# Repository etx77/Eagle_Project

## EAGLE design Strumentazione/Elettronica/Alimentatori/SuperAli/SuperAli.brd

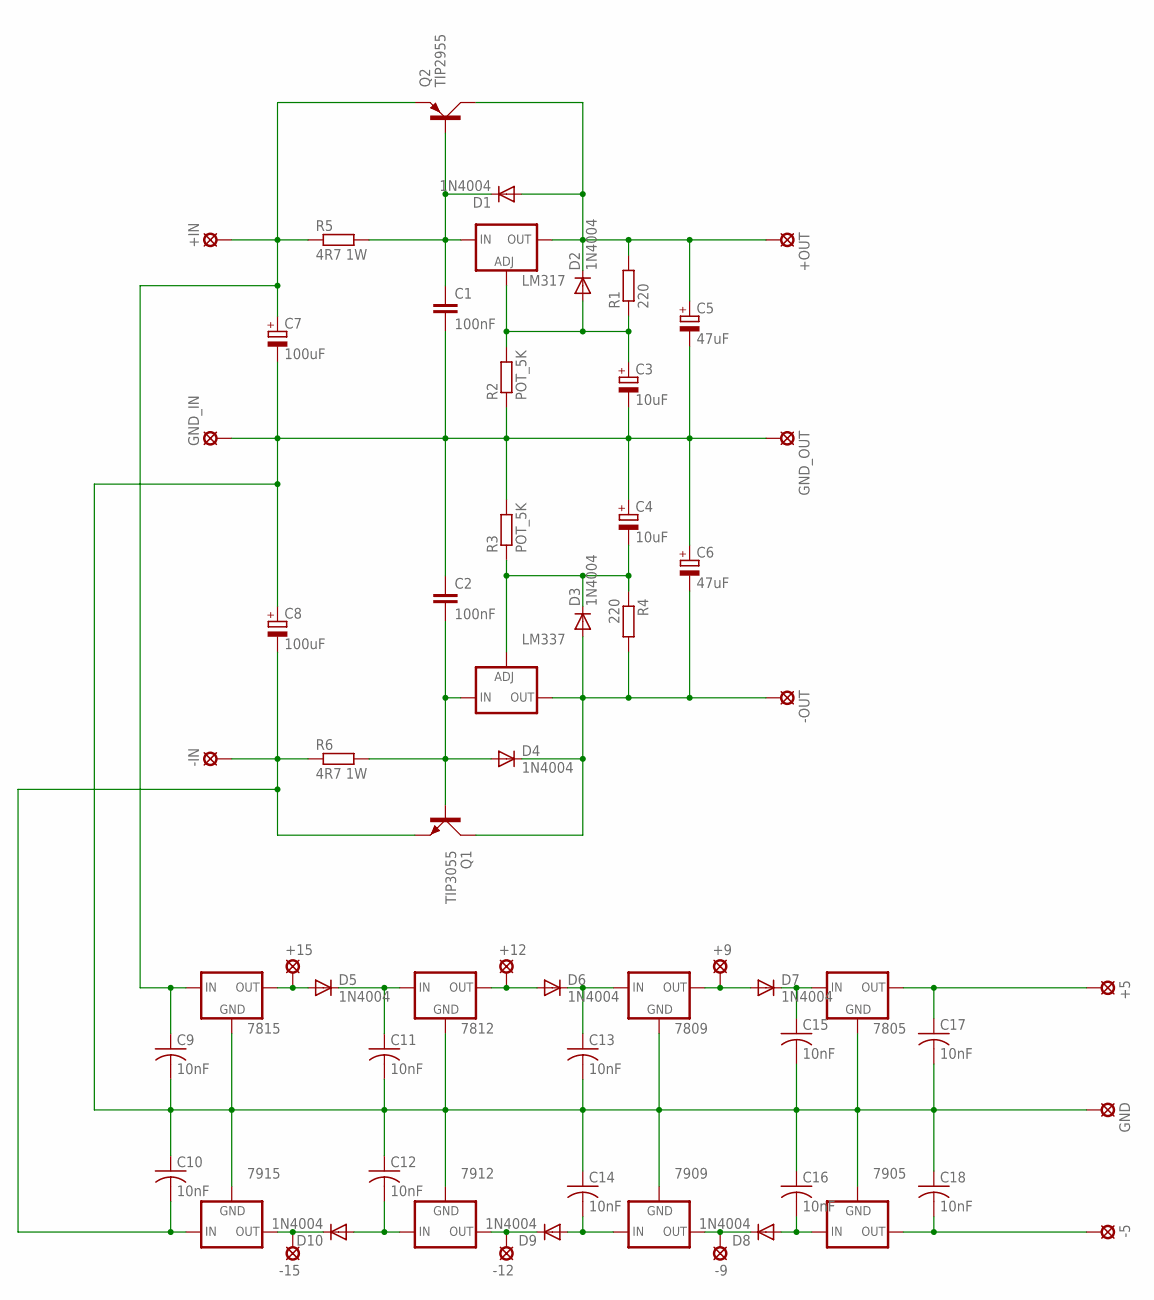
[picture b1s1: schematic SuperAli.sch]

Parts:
7805, 7809, 7812, 7815: 78XXS
7905, 7909, 7912, 7915: 79XXS
+5, +9, +12, +15: LSP10
+IN: LSP13
+OUT: LSP13
-5, -9, -12, -15: LSP10
-IN: LSP13
-OUT: LSP13
C1, C2: 100nF; C025-040X050
C3, C4: 10uF; E2-5
C5, C6: 47uF; E3,5-10
C7, C8: 100uF; E7,5-16
C9, C10, C11, C12, C13, C14, C15, C16, C17, C18: 10nF; C025-025X050
D1, D2, D3, D4, D5, D6, D7, D8, D9, D10: 1N4004; DO41-10
GND: LSP10
GND_IN: LSP13
GND_OUT: LSP13
LM317: LM317TS; 317TS
LM337: LM337TS; 337TS
Q1: TIP3055; TOP3AV
Q2: TIP2955; TOP3AV
R1, R4: 220; 0207/7
R2, R3: POT_5K; 0207/7
R5, R6: 4R7 1W; 0617/17

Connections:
7809: 7809.OUT, +9.MP, D7.A
unnamed: C3.+, D2.A, LM317.1 (ADJ), R1.1, R2.2
unnamed: C2.2, D4.A, LM337.2 (IN), Q1.B, R6.2
unnamed: C4.-, D3.C, LM337.1 (ADJ), R3.1, R4.1
unnamed: C1.1, D1.C, LM317.3 (IN), Q2.B, R5.2
unnamed: -OUT.MP, C6.-, D3.A, D4.C, LM337.3 (OUT), Q1.C, R4.2
unnamed: 7815.IN, +IN.MP, C7.+, C9.1, Q2.E, R5.1
unnamed: 7805.GND, 7809.GND, 7812.GND, 7815.GND, 7905.GND, 7909.GND, 7912.GND, 7915.GND, C1.2, C2.1, C3.-, C4.+, C5.-, C6.+, C7.-, C8.+, C9.2, C10.1, C11.2, C12.1, C13.2, C14.1, C15.2, C16.1, C17.2, C18.1, GND.MP, GND_IN.MP, GND_OUT.MP, R2.1, R3.2
unnamed: 7915.IN, -IN.MP, C8.-, C10.2, Q1.E, R6.1
unnamed: +OUT.MP, C5.+, D1.A, D2.C, LM317.2 (OUT), Q2.C, R1.2
unnamed: 7805.OUT, +5.MP, C17.1
unnamed: 7905.OUT, -5.MP, C18.2
unnamed: 7805.IN, C15.1, D7.C
unnamed: 7905.IN, C16.2, D8.A
unnamed: 7909.OUT, -9.MP, D8.C
unnamed: 7809.IN, C13.1, D6.C
unnamed: 7909.IN, C14.2, D9.A
unnamed: 7912.OUT, -12.MP, D9.C
unnamed: 7812.OUT, +12.MP, D6.A
unnamed: 7812.IN, C11.1, D5.C
unnamed: 7815.OUT, +15.MP, D5.A
unnamed: 7915.OUT, -15.MP, D10.C
unnamed: 7912.IN, C12.2, D10.A

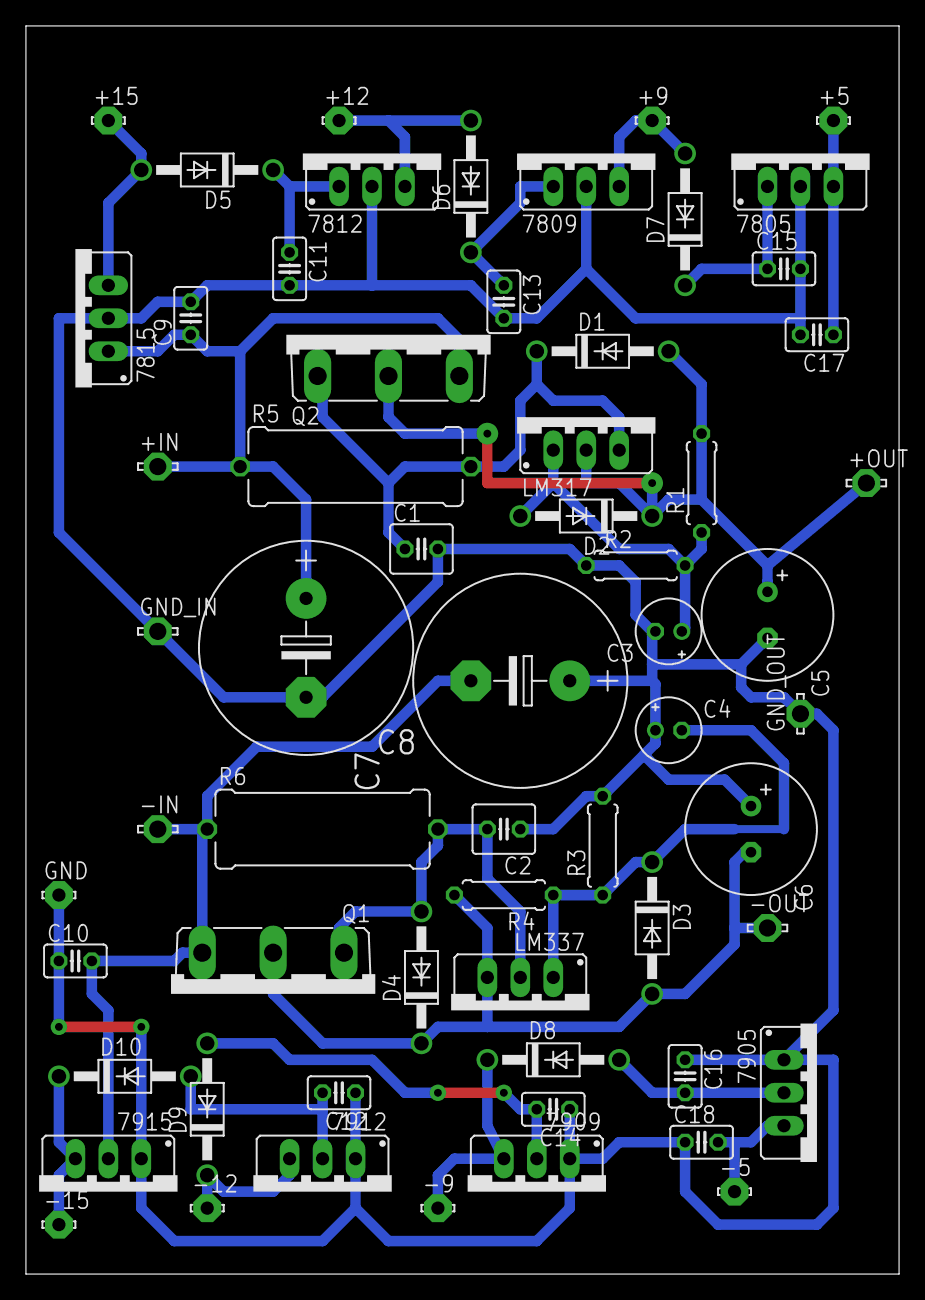
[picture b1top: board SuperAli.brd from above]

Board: 2 copper layers, 67.3 x 96.2 mm, 61 parts (0 on the bottom side), 23 nets.

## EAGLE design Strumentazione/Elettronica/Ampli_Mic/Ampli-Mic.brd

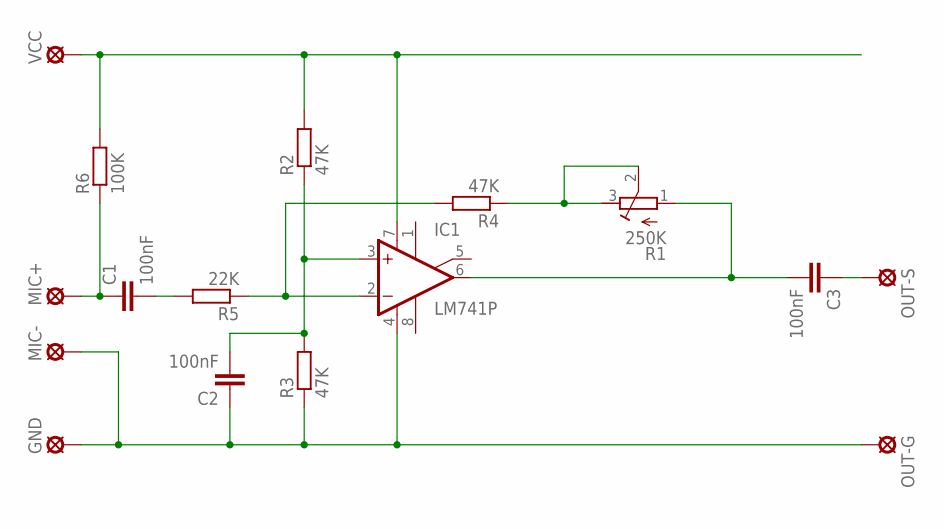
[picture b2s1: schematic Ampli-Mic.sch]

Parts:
C1, C2, C3: 100nF; C050-024X044
GND: LSP10
IC1: LM741P; DIL08
MIC+: LSP10
MIC-: LSP10
OUT-G: LSP10
OUT-S: LSP10
R1: 250K; RTRIM3339P
R2, R3, R4: 47K; 0207/10
R5: 22K; 0207/10
R6: 100K; 0207/10
VCC: LSP10

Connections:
unnamed: C2.1, GND.MP, IC1.4 (V-), MIC-.MP, OUT-G.MP, R3.1
unnamed: IC1.7 (V+), R2.2, R6.2, VCC.MP
unnamed: C2.2, IC1.3 (+IN), R2.1, R3.2
unnamed: IC1.2 (-IN), R4.2, R5.1
unnamed: R1.2 (S), R1.3 (E), R4.1
unnamed: C3.1, OUT-S.MP
unnamed: C3.2, IC1.6 (OUT), R1.1 (A)
unnamed: C1.2, R5.2
unnamed: C1.1, MIC+.MP, R6.1

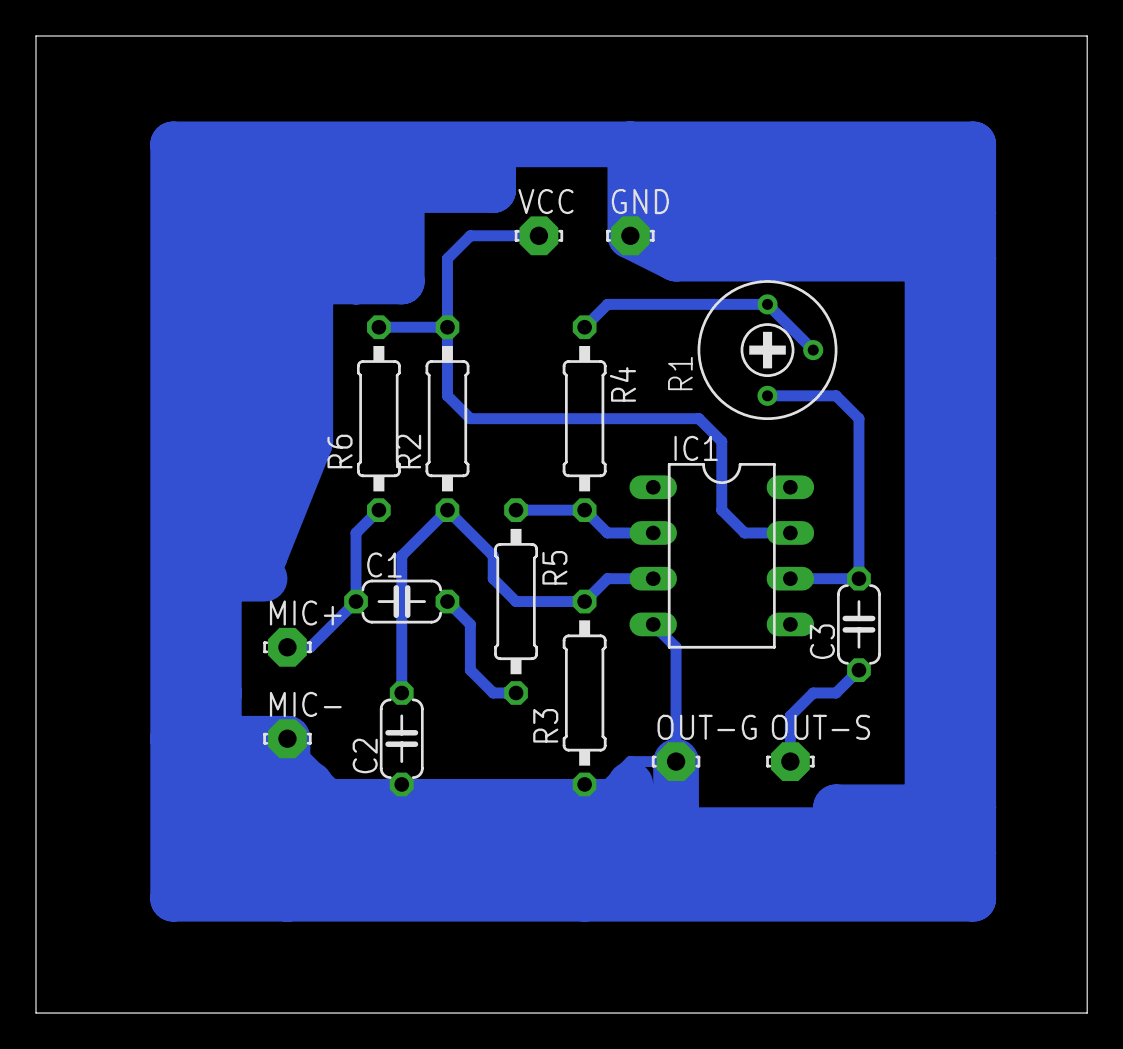
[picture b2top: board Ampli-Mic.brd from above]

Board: 2 copper layers, 58.4 x 54.3 mm, 16 parts (0 on the bottom side), 9 nets.

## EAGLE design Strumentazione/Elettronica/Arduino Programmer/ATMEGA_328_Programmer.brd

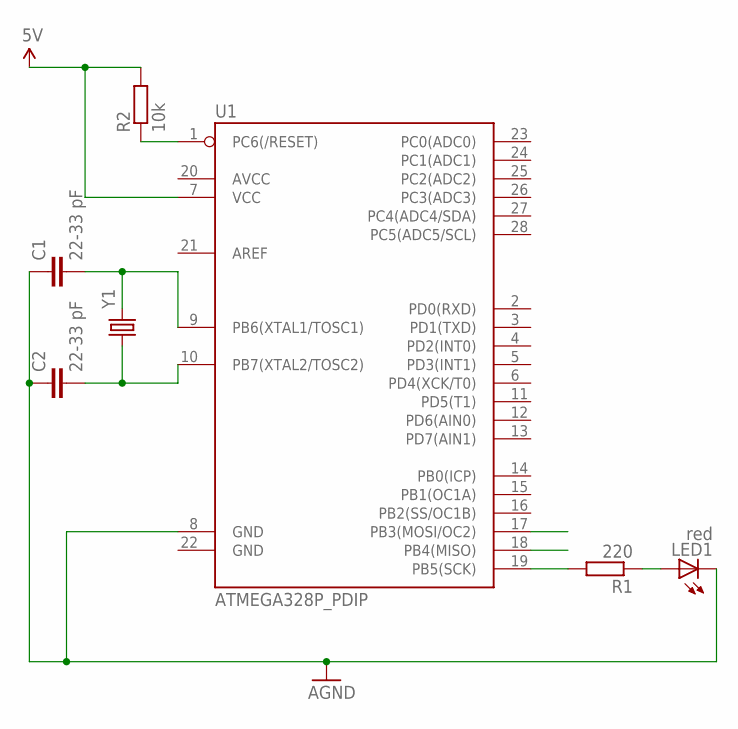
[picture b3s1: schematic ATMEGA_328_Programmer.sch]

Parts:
C1, C2: 22-33 pF; AXIAL-5MM
LED1: red; LED3MM
R1: 220; 0204/7
R2: 10k; 0204/7
U1: ATMEGA328P_PDIP; DIL28-3
Y1: CRYSTALHC49US; HC49US

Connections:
5V: R2.2, U1.7 (VCC)
AGND: C1.P$1 (1), C2.P$1 (1), LED1.K (C), U1.8 (GND)
unnamed: R1.2, U1.19 (PB5(SCK))
unnamed: LED1.A, R1.1
unnamed: C1.P$2 (2), U1.9 (PB6(XTAL1/TOSC1)), Y1.2
unnamed: R2.1, U1.1 (PC6(/RESET))
unnamed: C2.P$2 (2), U1.10 (PB7(XTAL2/TOSC2)), Y1.1

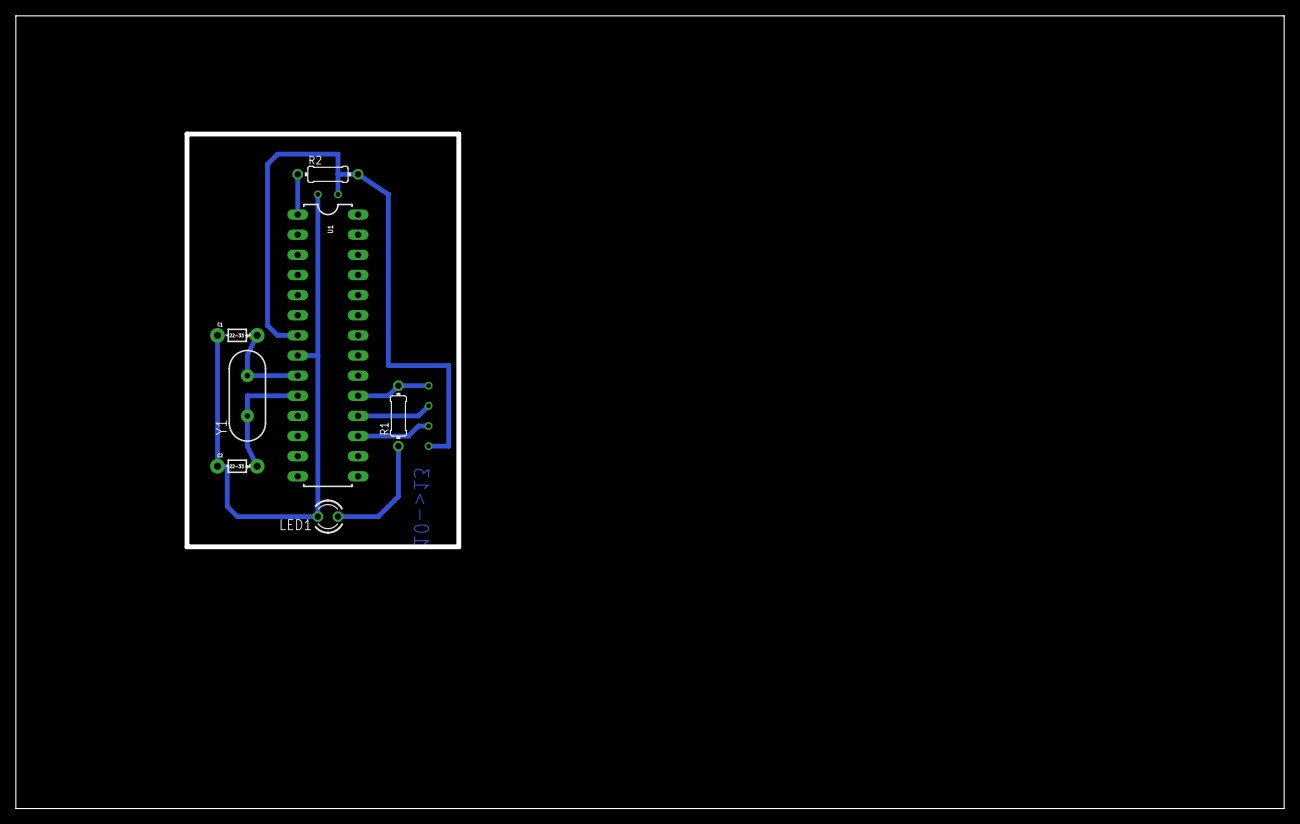
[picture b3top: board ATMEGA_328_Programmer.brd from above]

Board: 2 copper layers, 160.0 x 100.0 mm, 7 parts (0 on the bottom side), 7 nets.

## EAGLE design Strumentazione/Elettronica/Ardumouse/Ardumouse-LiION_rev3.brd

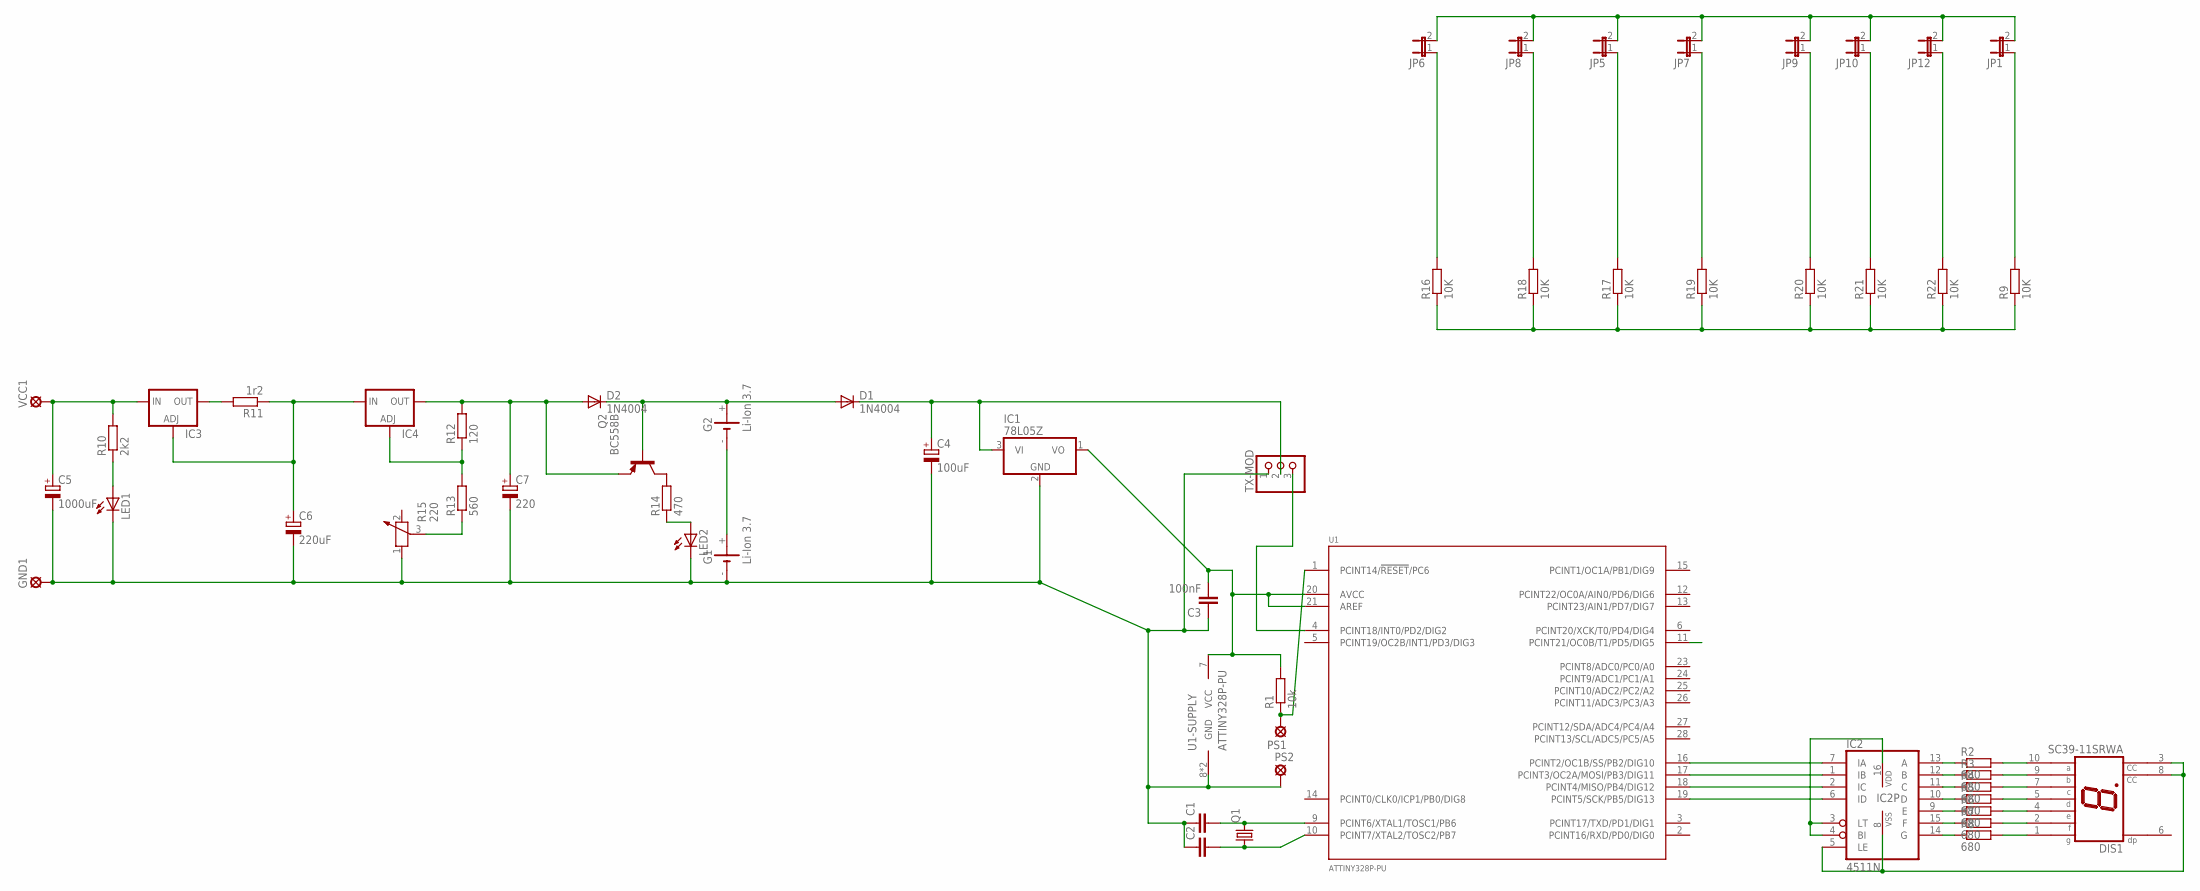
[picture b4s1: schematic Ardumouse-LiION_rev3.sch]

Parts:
C1, C2: C2,5-3; C2.5-3
C3: 100nF; C2.5-3
C4: 100uF; E3,5-8
C5: 1000uF; E3,5-8
C6: 220uF; E3,5-8
C7: 220; E3,5-8
D1, D2: 1N4004; DO41-10
DIS1: SC39-11SRWA; HDSP-E
G1, G2: Li-Ion 3.7; SL-160AA/PR
GND1: LSP13
IC1: 78L05Z; TO92
IC2: 4511N; DIL16
IC3, IC4: LM317TS; 317TS
JP1, JP5, JP6, JP7, JP8, JP9, JP10, JP12: JP1E; JP1
LED1, LED2: LED5MM
PS1, PS2: LSP10
Q1: CRYSTALHC49S; HC49/S
Q2: BC558B; TO92-EBC
R1: 10k; 0204/7
R2, R3, R4, R5, R6, R7, R8: 680; 0204/7
R9, R16, R17, R18, R19, R20, R21, R22: 10K; 0204/7
R10: 2k2; 0207/7
R11: 1r2; 0207/7
R12: 120; 0207/7
R13: 560; 0207/7
R14: 470; 0207/7
R15: 220; PT-10
TX-MOD: PINHD-1X3; 1X03
U1: ATTINY328P-PU; DIP-28
VCC1: LSP13

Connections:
DISA: C3.2, IC1.1 (VO), R1.2, U1.7 (VCC), U1.20 (AVCC), U1.21 (AREF)
unnamed: C1.2, Q1.2, U1.9 (PCINT6/XTAL1/TOSC1/PB6)
unnamed: C2.2, Q1.1, U1.10 (PCINT7/XTAL2/TOSC2/PB7)
unnamed: C4.+, D1.C, IC1.3 (VI), TX-MOD.2
unnamed: LED1.A, R10.1
unnamed: TX-MOD.3, U1.4 (PCINT18/INT0/PD2/DIG2)
unnamed: IC2.13 (A), R2.1
unnamed: PS1.MP, R1.1, U1.1 (PCINT14/!RESET!/PC6)
unnamed: IC2.7 (IA), U1.16 (PCINT2/OC1B/SS/PB2/DIG10)
unnamed: DIS1.3 (CC), DIS1.8 (CC), IC2.5 (LE), IC2.8 (VSS)
unnamed: IC2.1 (IB), U1.17 (PCINT3/OC2A/MOSI/PB3/DIG11)
unnamed: IC2.2 (IC), U1.18 (PCINT4/MISO/PB4/DIG12)
unnamed: IC2.12 (B), R3.1
unnamed: IC2.11 (C), R4.1
unnamed: IC2.10 (D), R5.1
unnamed: IC2.9 (E), R6.1
unnamed: IC2.15 (F), R7.1
unnamed: IC2.14 (G), R8.1
unnamed: DIS1.10 (A), R2.2
unnamed: DIS1.9 (B), R3.2
unnamed: DIS1.7 (C), R4.2
unnamed: DIS1.5 (D), R5.2
unnamed: DIS1.4 (E), R6.2
unnamed: DIS1.2 (F), R7.2
unnamed: DIS1.1 (G), R8.2
unnamed: IC2.6 (ID), U1.19 (PCINT5/SCK/PB5/DIG13)
unnamed: JP1.1, R9.2
unnamed: IC2.3 (LT), IC2.4 (BI), IC2.16 (VDD)
unnamed: C5.+, IC3.3 (IN), R10.2, VCC1.MP
unnamed: IC3.2 (OUT), R11.2
unnamed: C6.+, IC3.1 (ADJ), IC4.3 (IN), R11.1
unnamed: JP6.1, R16.2
unnamed: R13.1, R15.3
unnamed: IC4.1 (ADJ), R12.1, R13.2
unnamed: C7.+, D2.A, IC4.2 (OUT), Q2.E, R12.2
unnamed: D1.A, D2.C, G2.+, Q2.B
unnamed: Q2.C, R14.2
unnamed: LED2.A, R14.1
unnamed: G1.+, G2.-
unnamed: JP5.1, R17.2
unnamed: JP8.1, R18.2
unnamed: JP9.1, R20.2
unnamed: JP10.1, R21.2
unnamed: JP12.1, R22.2
unnamed: R9.1, R16.1, R17.1, R18.1, R19.1, R20.1, R21.1, R22.1
unnamed: JP1.2, JP5.2, JP6.2, JP7.2, JP8.2, JP9.2, JP10.2, JP12.2
unnamed: JP7.1, R19.2
unnamed: C1.1, C2.1, C3.1, C4.-, C5.-, C6.-, C7.-, G1.-, GND1.MP, IC1.2 (GND), LED1.K (C), LED2.K (C), PS2.MP, R15.1, TX-MOD.1, U1.8 (GND), U1.22 (GND)

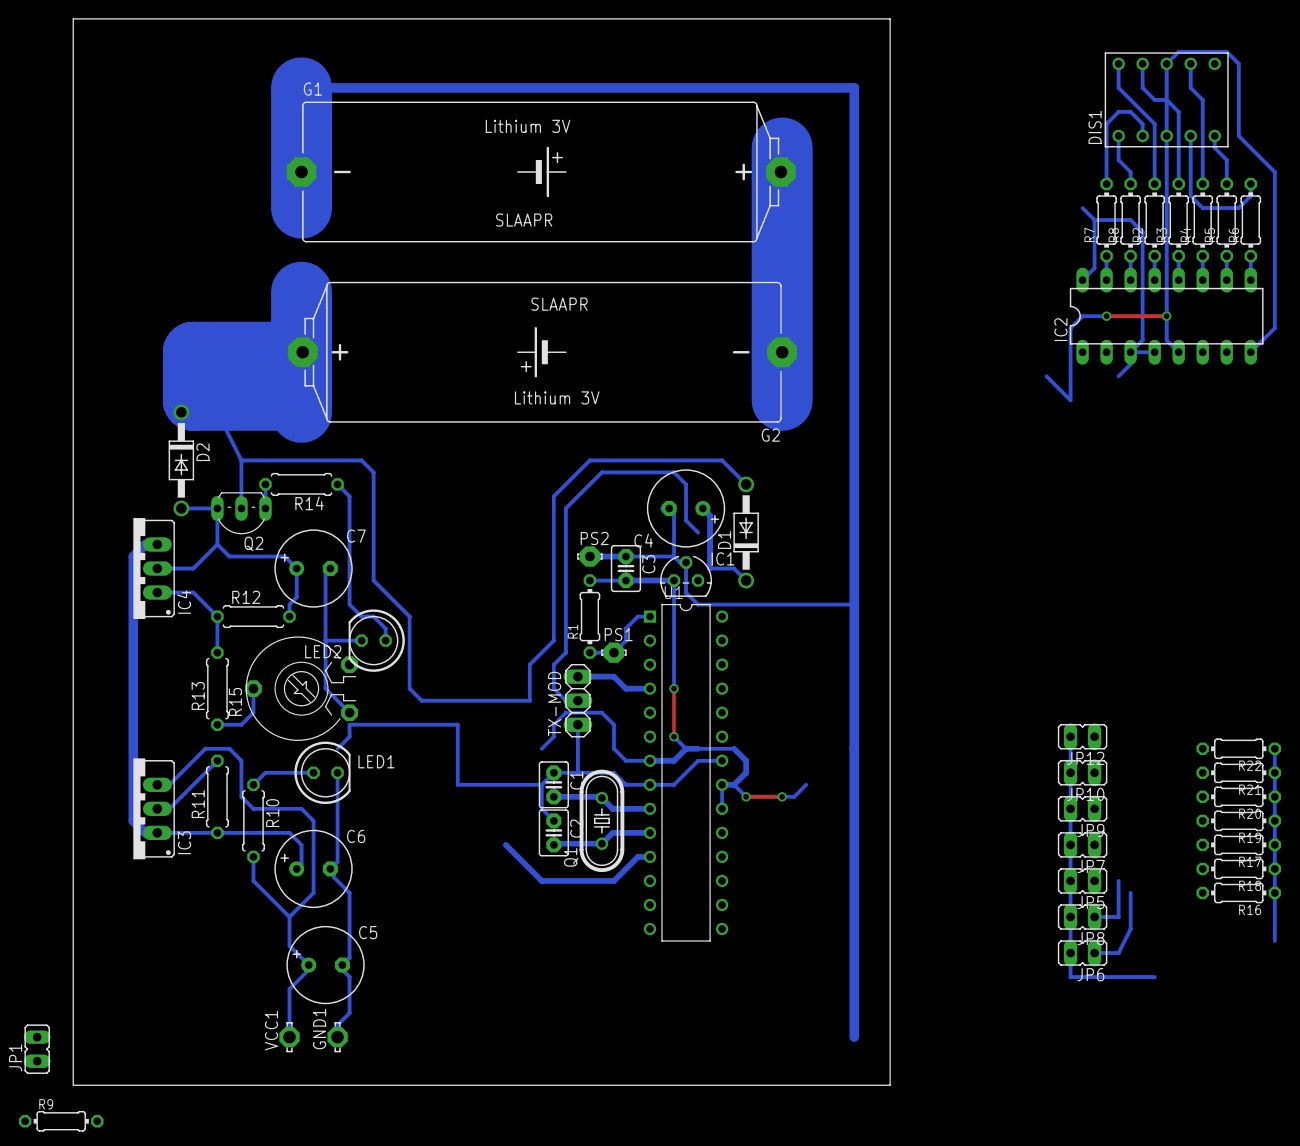
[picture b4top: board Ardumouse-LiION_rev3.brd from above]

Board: 2 copper layers, 86.3 x 112.7 mm, 56 parts (0 on the bottom side), 48 nets.

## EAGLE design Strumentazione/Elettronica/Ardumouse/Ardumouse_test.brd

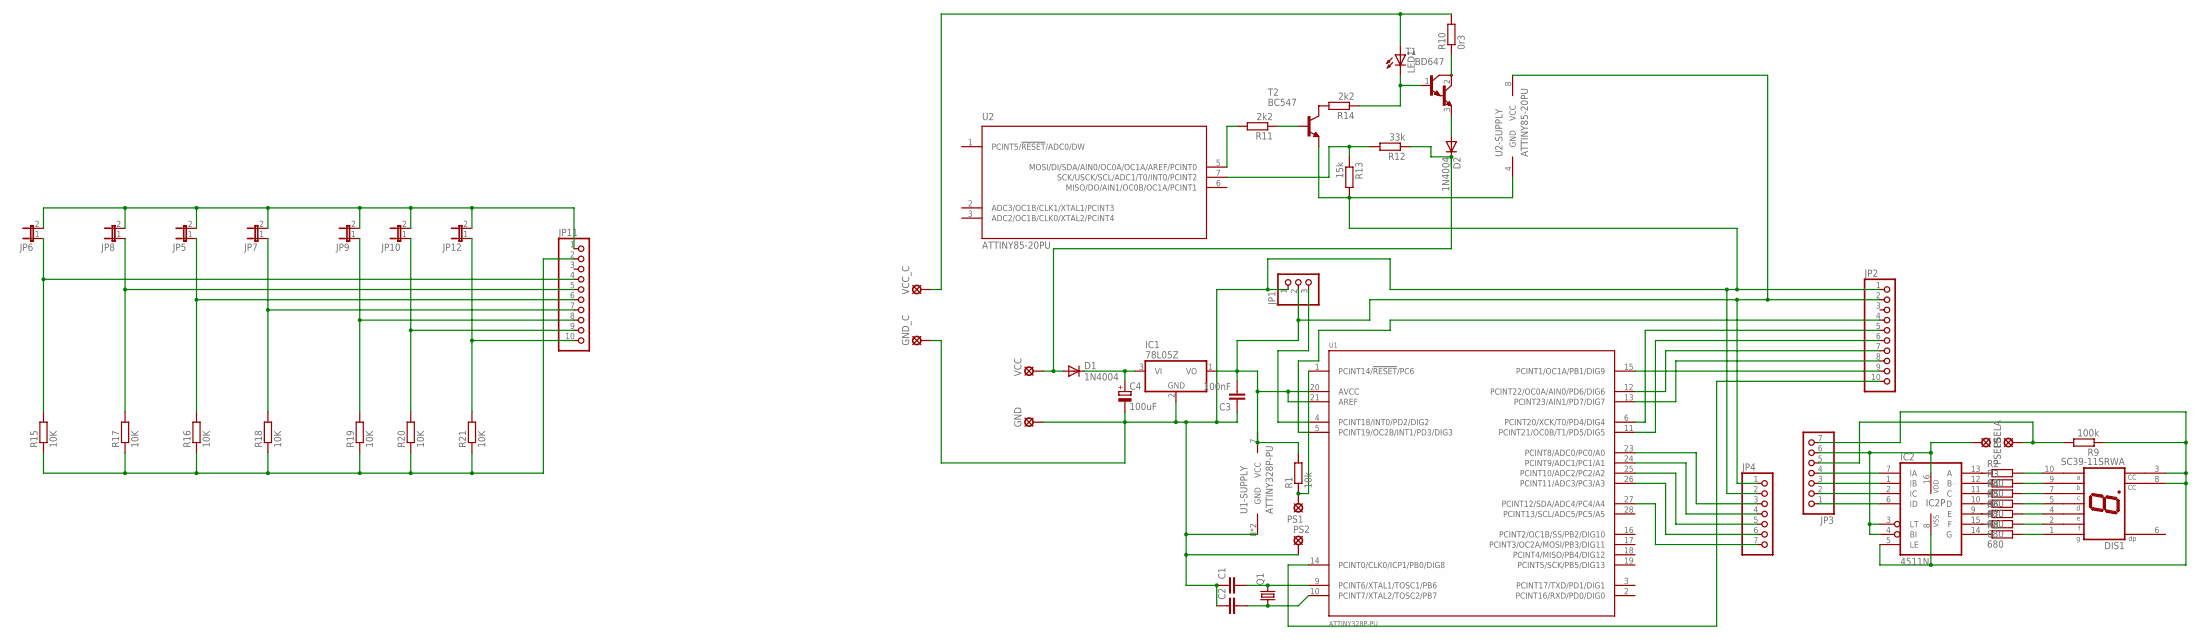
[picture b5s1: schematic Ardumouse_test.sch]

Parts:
C1, C2: C2,5-3; C2.5-3
C3: 100nF; C2.5-3
C4: 100uF; E3,5-8
D1, D2: 1N4004; DO41-10
DIS1: SC39-11SRWA; HDSP-E
GND: LSP10
GND_C: LSP10
IC1: 78L05Z; TO92
IC2: 4511N; DIL16
JP1: PINHD-1X3; 1X03
JP2, JP11: PINHD-1X10; 1X10
JP3, JP4: PINHD-1X7; 1X07
JP5, JP6, JP7, JP8, JP9, JP10, JP12: JP1E; JP1
LED1: LED5MM
PS1, PS2: LSP10
PSELA: LSP10
PSELB: LSP10
Q1: CRYSTALHC49S; HC49/S
R1: 10k; 0204/7
R2, R3, R4, R5, R6, R7, R8: 680; 0204/7
R9: 100k; 0204/7
R10: 0r3; 0204/7
R11, R14: 2k2; 0204/7
R12: 33k; 0204/7
R13: 15k; 0204/7
R15, R16, R17, R18, R19, R20, R21: 10K; 0204/7
T1: BD647; TO220
T2: BC547; TO92
U1: ATTINY328P-PU; DIP-28
U2: ATTINY85-20PU; DIP-8
VCC: LSP10
VCC_C: LSP10

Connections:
unnamed: C1.2, Q1.2, U1.9 (PCINT6/XTAL1/TOSC1/PB6)
unnamed: C2.2, Q1.1, U1.10 (PCINT7/XTAL2/TOSC2/PB7)
unnamed: D1.A, D2.C, R12.1, VCC.MP
unnamed: C4.+, D1.C, IC1.3 (VI)
unnamed: JP6.1, JP11.4, R15.2
unnamed: JP5.1, JP11.6, R16.2
unnamed: JP1.3, U1.4 (PCINT18/INT0/PD2/DIG2)
unnamed: JP2.4, U1.5 (PCINT19/OC2B/INT1/PD3/DIG3)
unnamed: JP2.5, U1.6 (PCINT20/XCK/T0/PD4/DIG4)
unnamed: JP2.6, U1.11 (PCINT21/OC0B/T1/PD5/DIG5)
unnamed: JP2.7, U1.12 (PCINT22/OC0A/AIN0/PD6/DIG6)
unnamed: JP2.8, U1.13 (PCINT23/AIN1/PD7/DIG7)
unnamed: JP2.9, U1.15 (PCINT1/OC1A/PB1/DIG9)
unnamed: JP2.10, U1.14 (PCINT0/CLK0/ICP1/PB0/DIG8)
unnamed: IC2.13 (A), R2.1
unnamed: PS1.MP, R1.1, U1.1 (PCINT14/!RESET!/PC6)
unnamed: JP3.5, PSELA.MP, R9.2
unnamed: DIS1.3 (CC), DIS1.8 (CC), IC2.5 (LE), IC2.8 (VSS), JP3.7, R9.1
unnamed: IC2.7 (IA), JP3.4
unnamed: IC2.1 (IB), JP3.3
unnamed: IC2.12 (B), R3.1
unnamed: IC2.11 (C), R4.1
unnamed: IC2.10 (D), R5.1
unnamed: IC2.9 (E), R6.1
unnamed: IC2.15 (F), R7.1
unnamed: IC2.14 (G), R8.1
unnamed: DIS1.10 (A), R2.2
unnamed: DIS1.9 (B), R3.2
unnamed: DIS1.7 (C), R4.2
unnamed: DIS1.5 (D), R5.2
unnamed: DIS1.4 (E), R6.2
unnamed: DIS1.2 (F), R7.2
unnamed: DIS1.1 (G), R8.2
unnamed: IC2.2 (IC), JP3.2
unnamed: IC2.6 (ID), JP3.1
unnamed: IC2.3 (LT), IC2.4 (BI), IC2.16 (VDD), JP3.6, PSELB.MP
unnamed: R12.2, R13.1, U2.7 (SCK/USCK/SCL/ADC1/T0/INT0/PCINT2)
unnamed: JP4.3, U1.23 (PCINT8/ADC0/PC0/A0)
unnamed: JP7.1, JP11.7, R18.2
unnamed: D2.A, T1.3 (E)
unnamed: JP4.5, U1.25 (PCINT10/ADC2/PC2/A2)
unnamed: JP4.6, U1.26 (PCINT11/ADC3/PC3/A3)
unnamed: JP4.7, U1.27 (PCINT12/SDA/ADC4/PC4/A4)
unnamed: R11.1, T2.2 (B)
unnamed: JP4.4, U1.24 (PCINT9/ADC1/PC1/A1)
unnamed: C1.1, C2.1, C3.1, C4.-, GND.MP, GND_C.MP, IC1.2 (GND), JP1.1, JP2.1, JP4.2, PS2.MP, R13.2, T2.1 (E), U1.8 (GND), U1.22 (GND), U2.4 (GND)
unnamed: LED1.A, R10.2, VCC_C.MP
unnamed: LED1.K (C), R14.1, T1.1 (B)
unnamed: R14.2, T2.3 (C)
unnamed: R10.1, T1.2 (C)
unnamed: C3.2, IC1.1 (VO), JP1.2, JP2.2, JP4.1, R1.2, U1.7 (VCC), U1.20 (AVCC), U1.21 (AREF), U2.8 (VCC)
unnamed: R11.2, U2.5 (MOSI/DI/SDA/AIN0/OC0A/OC1A/AREF/PCINT0)
unnamed: JP8.1, JP11.5, R17.2
unnamed: JP9.1, JP11.8, R19.2
unnamed: JP10.1, JP11.9, R20.2
unnamed: JP11.10, JP12.1, R21.2
unnamed: JP11.2, R15.1, R16.1, R17.1, R18.1, R19.1, R20.1, R21.1
unnamed: JP5.2, JP6.2, JP7.2, JP8.2, JP9.2, JP10.2, JP11.1, JP12.2

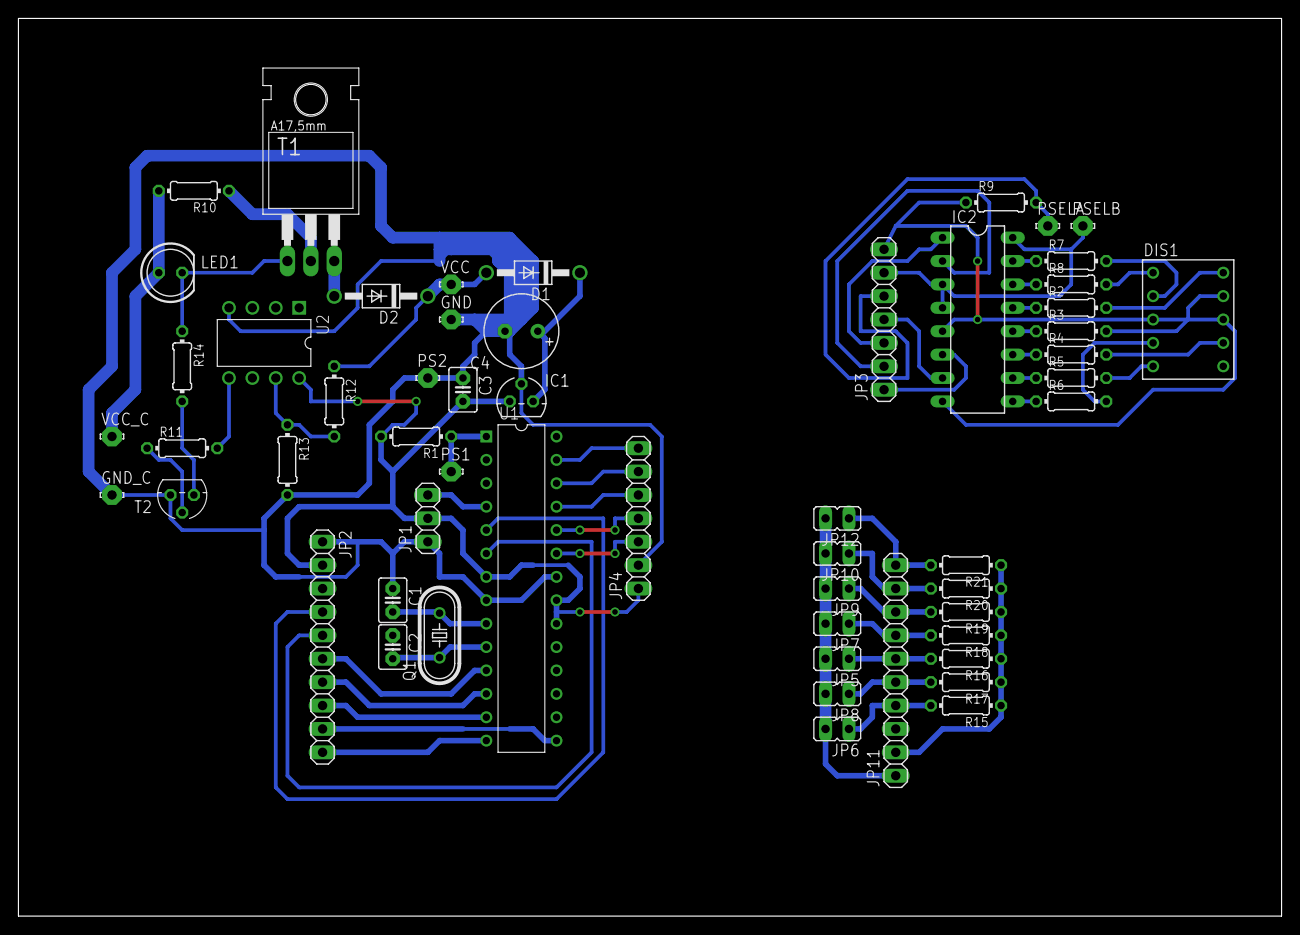
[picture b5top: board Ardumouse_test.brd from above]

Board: 2 copper layers, 137.1 x 97.5 mm, 56 parts (0 on the bottom side), 58 nets.

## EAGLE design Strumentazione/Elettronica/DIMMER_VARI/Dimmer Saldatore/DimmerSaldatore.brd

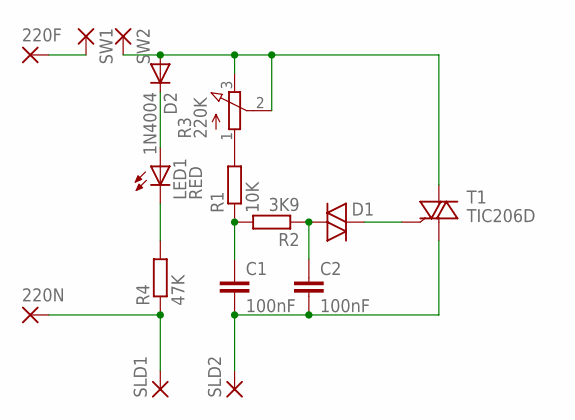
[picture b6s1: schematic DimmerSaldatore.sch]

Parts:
220F, 220N: 3,81/1,4
C1, C2: 100nF; C075-052X106
D1: DIAC-GT32; GT32
D2: 1N4004; DO41-10
LED1: RED; LED5MM
R1: 10K; 0204/7
R2: 3K9; 0204/7
R3: 220K; 3RP/1610N
R4: 47K; 0204/7
SLD1, SLD2: 3,81/1,4
SW1, SW2: 3,81/1,4
T1: TIC206D; TO220BV

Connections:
unnamed: D1.2, T1.G
unnamed: C2.1, D1.1, R2.1
unnamed: C1.1, R1.1, R2.2
unnamed: R1.2, R3.1 (A)
unnamed: D2.A, R3.2 (S), R3.3 (E), SW2.1, T1.T2 (A2)
unnamed: 220N.1, R4.1, SLD1.1
unnamed: D2.C, LED1.A
unnamed: LED1.K (C), R4.2
unnamed: 220F.1, SW1.1
unnamed: C1.2, C2.2, SLD2.1, T1.T1 (A1)

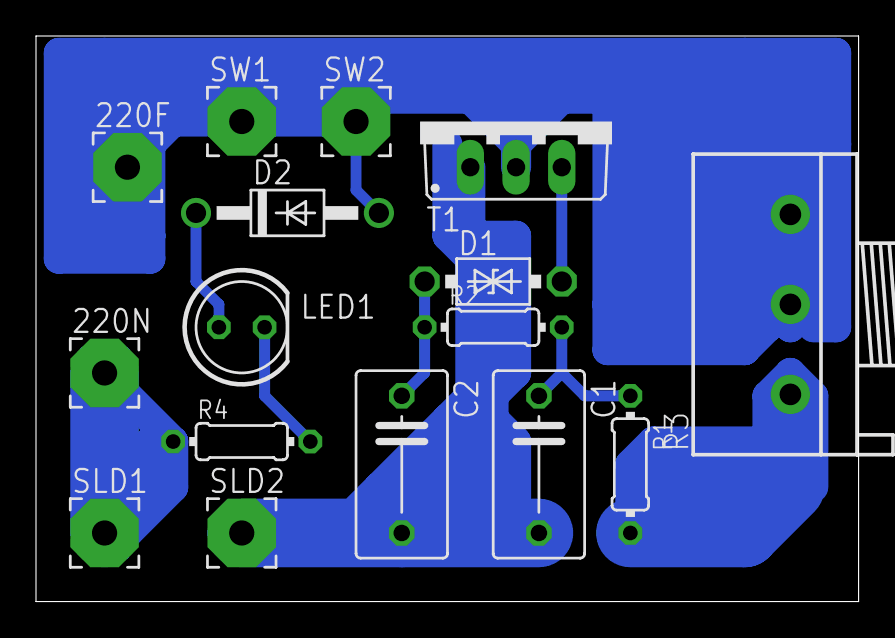
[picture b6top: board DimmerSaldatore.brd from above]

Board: 2 copper layers, 45.7 x 31.4 mm, 16 parts (0 on the bottom side), 10 nets.

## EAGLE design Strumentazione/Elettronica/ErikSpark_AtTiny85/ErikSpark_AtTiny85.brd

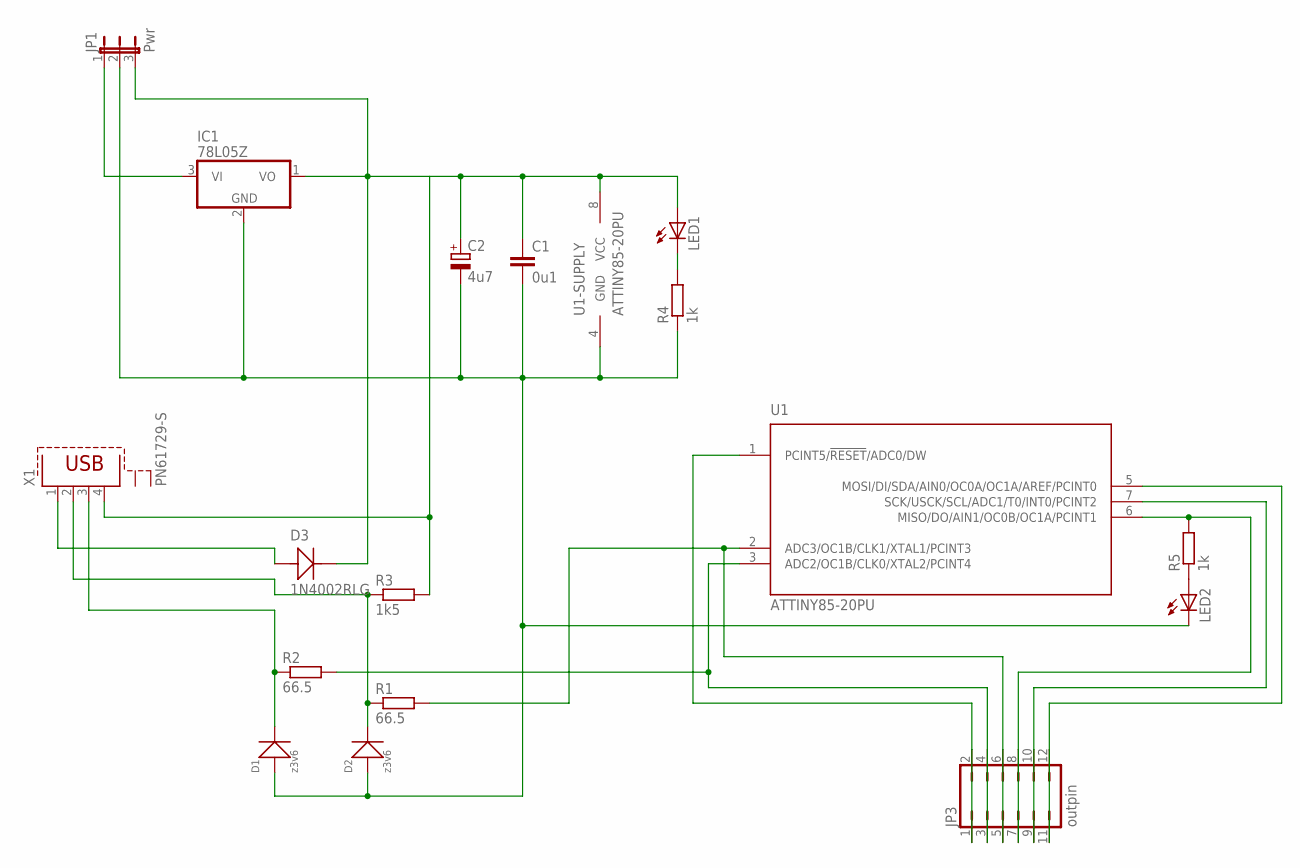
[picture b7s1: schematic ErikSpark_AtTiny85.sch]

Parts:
C1: 0u1; C050-024X044
C2: 4u7; E2-4
D1, D2: z3v6; DO-35
D3: 1N4002RLG; DO-41
IC1: 78L05Z; TO92
JP1: Pwr; JP2
JP3: outpin; JP6Q
LED1, LED2: LED3MM
R1, R2: 66.5; 0207/15
R3: 1k5; 0207/15
R4, R5: 1k; 0207/15
U1: ATTINY85-20PU; DIP-8
X1: PN61729-S

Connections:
unnamed: C1.2, C2.-, D1.A (+), D2.A (+), IC1.2 (GND), JP1.2, LED2.K (C), R4.1, U1.4 (GND)
unnamed: D3.A, X1.1
unnamed: JP3.3, JP3.4, R2.2, U1.3 (ADC2/OC1B/CLK0/XTAL2/PCINT4)
unnamed: JP3.5, JP3.6, R1.2, U1.2 (ADC3/OC1B/CLK1/XTAL1/PCINT3)
unnamed: JP3.7, JP3.8, R5.2, U1.6 (MISO/DO/AIN1/OC0B/OC1A/PCINT1)
unnamed: JP3.9, JP3.10, U1.7 (SCK/USCK/SCL/ADC1/T0/INT0/PCINT2)
unnamed: JP3.11, JP3.12, U1.5 (MOSI/DI/SDA/AIN0/OC0A/OC1A/AREF/PCINT0)
unnamed: JP3.1, JP3.2, U1.1 (PCINT5/!RESET!/ADC0/DW)
unnamed: LED2.A, R5.1
unnamed: LED1.K (C), R4.2
unnamed: D1.C (-), R2.1, X1.3
unnamed: D2.C (-), R1.1, R3.1, X1.2
unnamed: C1.1, C2.+, D3.C, IC1.1 (VO), JP1.3, LED1.A, R3.2, U1.8 (VCC), X1.4
unnamed: IC1.3 (VI), JP1.1

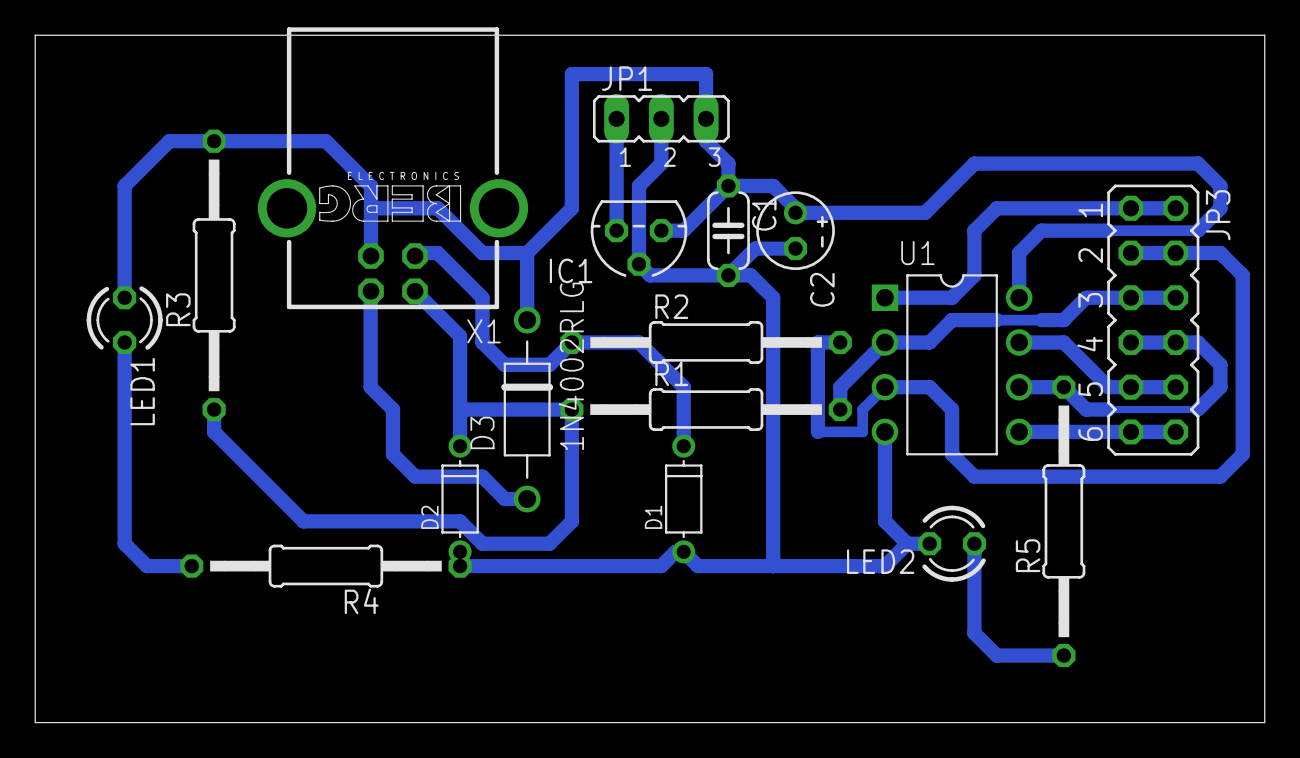
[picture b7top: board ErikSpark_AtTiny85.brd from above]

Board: 2 copper layers, 69.8 x 39.0 mm, 17 parts (0 on the bottom side), 14 nets.

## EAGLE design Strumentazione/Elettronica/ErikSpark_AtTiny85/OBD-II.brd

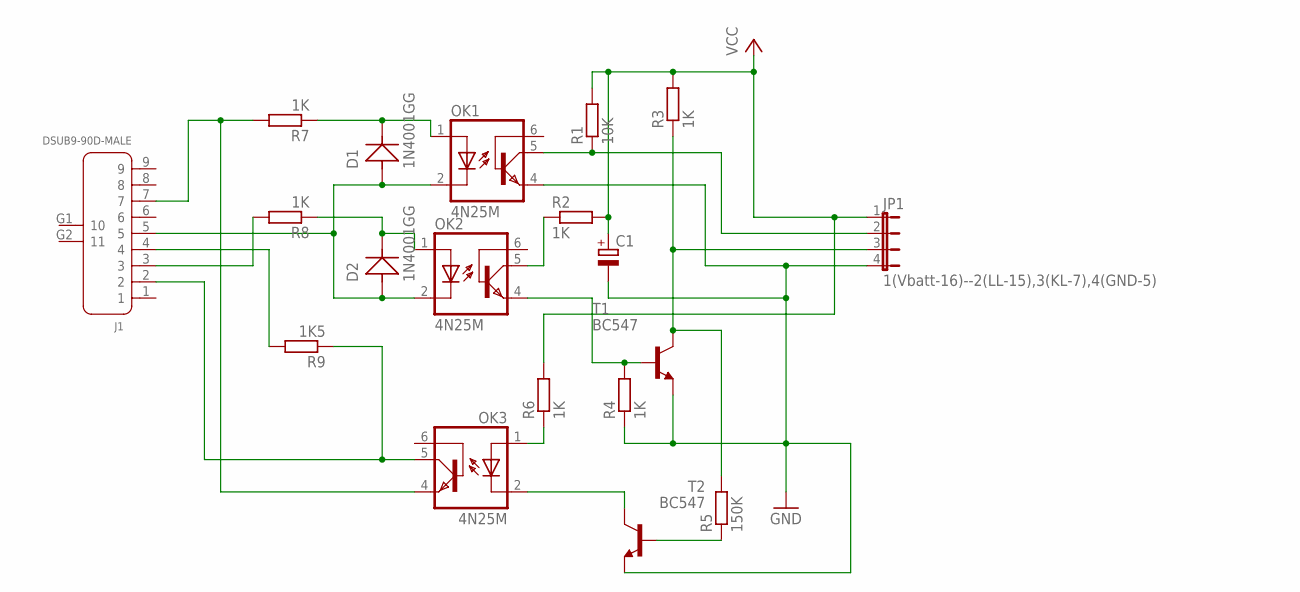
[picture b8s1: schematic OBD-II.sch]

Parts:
C1: CPOL-EUE2-5; E2-5
D1, D2: 1N4001GG; DO-41
J1: DSUB9-90D-MALE; DSUB9+2P-2.77-90D-MALE
JP1: 1(Vbatt-16)--2(LL-15),3(KL-7),4(GND-5); JP4
OK1, OK2, OK3: 4N25M; DIL06
R1: 10K; 0207/10
R2, R3, R4, R6, R7, R8: 1K; 0207/10
R5: 150K; 0207/10
R9: 1K5; 0207/10
T1, T2: BC547; TO92

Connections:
GND: C1.-, JP1.4, OK1.4 (EMI), R4.1, T1.1 (E), T2.1 (E)
unnamed: JP1.2, OK1.5 (COL), R1.1
unnamed: J1.2, OK3.5 (COL), R9.1
unnamed: J1.4, R9.2
unnamed: J1.3, R8.2
unnamed: OK2.5 (COL), R2.1
unnamed: JP1.3, R3.1, R5.2, T1.3 (C)
unnamed: OK2.4 (EMI), R4.2, T1.2 (B)
unnamed: J1.7, OK3.4 (EMI), R7.2
unnamed: R5.1, T2.2 (B)
unnamed: OK3.1 (A), R6.1
unnamed: D1.A, D2.A, J1.5, OK1.2 (C), OK2.2 (C)
unnamed: OK3.2 (C), T2.3 (C)
unnamed: D2.C, OK2.1 (A), R8.1
unnamed: D1.C, OK1.1 (A), R7.1
VCC: C1.+, JP1.1, R1.2, R2.2, R3.2, R6.2

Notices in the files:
parts and their libraries:
SparkFun-Capacitors: Licensing: Creative Commons ShareAlike 4.0 International - https://creativecommons.org/licenses/by-sa/4.0
volks73-Atmel: Creative Commons Attribution-ShareAlike 3.0 Unported (CC BY-SA 3.0), http://creativecommons.org/licenses/by-sa/3.0/.
